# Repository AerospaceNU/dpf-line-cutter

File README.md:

# Line Cutter: For Cutting Lines
The line cutter is a system for deploying a single parachute as both drogue and main. Reefing lines are used to constrict the parachute to two intermediate sizes, and these lines are threaded through line cutters. At the set altitudes (or after a time delay), nichrome wires burn through the reefing lines.

## Organization
* `code`: Line cutter code and flight data analyses.
  * `launch archive`: Raw flight data and summaries of successes/failures from past line cutter flights. Subfolders should be named with ISO date and launch site.
  * `libraries and drivers`: Should be obsolete soon (drivers etc. will be published as Arduino libraries).
    * `openocd_windows.zip`: Windows build of openOCD with nrf52940 bootloader and cheap st-link config packaged.
  * `tests`: Code that is useful for testing various line cutter features across hardware versions.
  * `v1`: Code for v1 perfboard line cutters.
  * `v2`: Code for mixed perfboard and PCB line cutters.
  * `v3`: Code for current PCB line cutters.
    * `bulk_erase`: Erases all data on flash chip.
    * `flash_reader`: Reads all data on flash chip.
    * `flight_variable_upload`: Sets parameters for flight.
    * `identifier`: Names PCB for Bluetooth advertising.
    * `InternalFS_format`: Erases files on NRF52840 and formats filesystem.
    * `line_cutter_v3`: Main program that runs on flights.
    * `memory_reader`: Reads state transition log.
* `docs`: More detailed documentation, see below for list.
* `schematic`: ECAD files for the line cutter hardware. Contains schematics for all line cutter hardware. Folder structure is described in the [readme](schematic/README.md)

## Documentation
Code documentation applies to the latest version (v1/v2 are not compatible with current line cutters).
* [`CHECKLIST`](docs/CHECKLIST.md): Pre-flight checklist for line cutter launches.
* [`FLASH`](docs/FLASH.md): Procedure for logging data to flash on line cutters.
* [`SIGNALS`](docs/SIGNALS.md): Description of current board.
* [`STATES`](docs/STATES.md): Description of state machine.
* [`nrf52_openocd`](docs/nrf52_openocd.md): Instructions for programming NRF52 chips with OpenOCD.

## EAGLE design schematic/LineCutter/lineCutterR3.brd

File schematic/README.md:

# Line cutter schematics

This folder is organized as follows:
  * `batt-and-reg.cam`: CAM file used for JLC
  * `lineCutterR<N>-.zip`: Production files sent to fab
  * `LineCutter`: eagle project containing all the actual files
    * `Line Cutter COTS.lbr`: common parts used (flash memory, nRF daughterboards, etc)
    * `lineCutterR1`: first PCB ordered (nRF52832, December 2020)
    * `lineCutterR2`: ESP32-S2 based, ordered spring 2021 (1 built, no software written for it)
    * `lineCutterR3`: nRF52840-based, ordered spring 2021. Flew Amesbury 3/20.

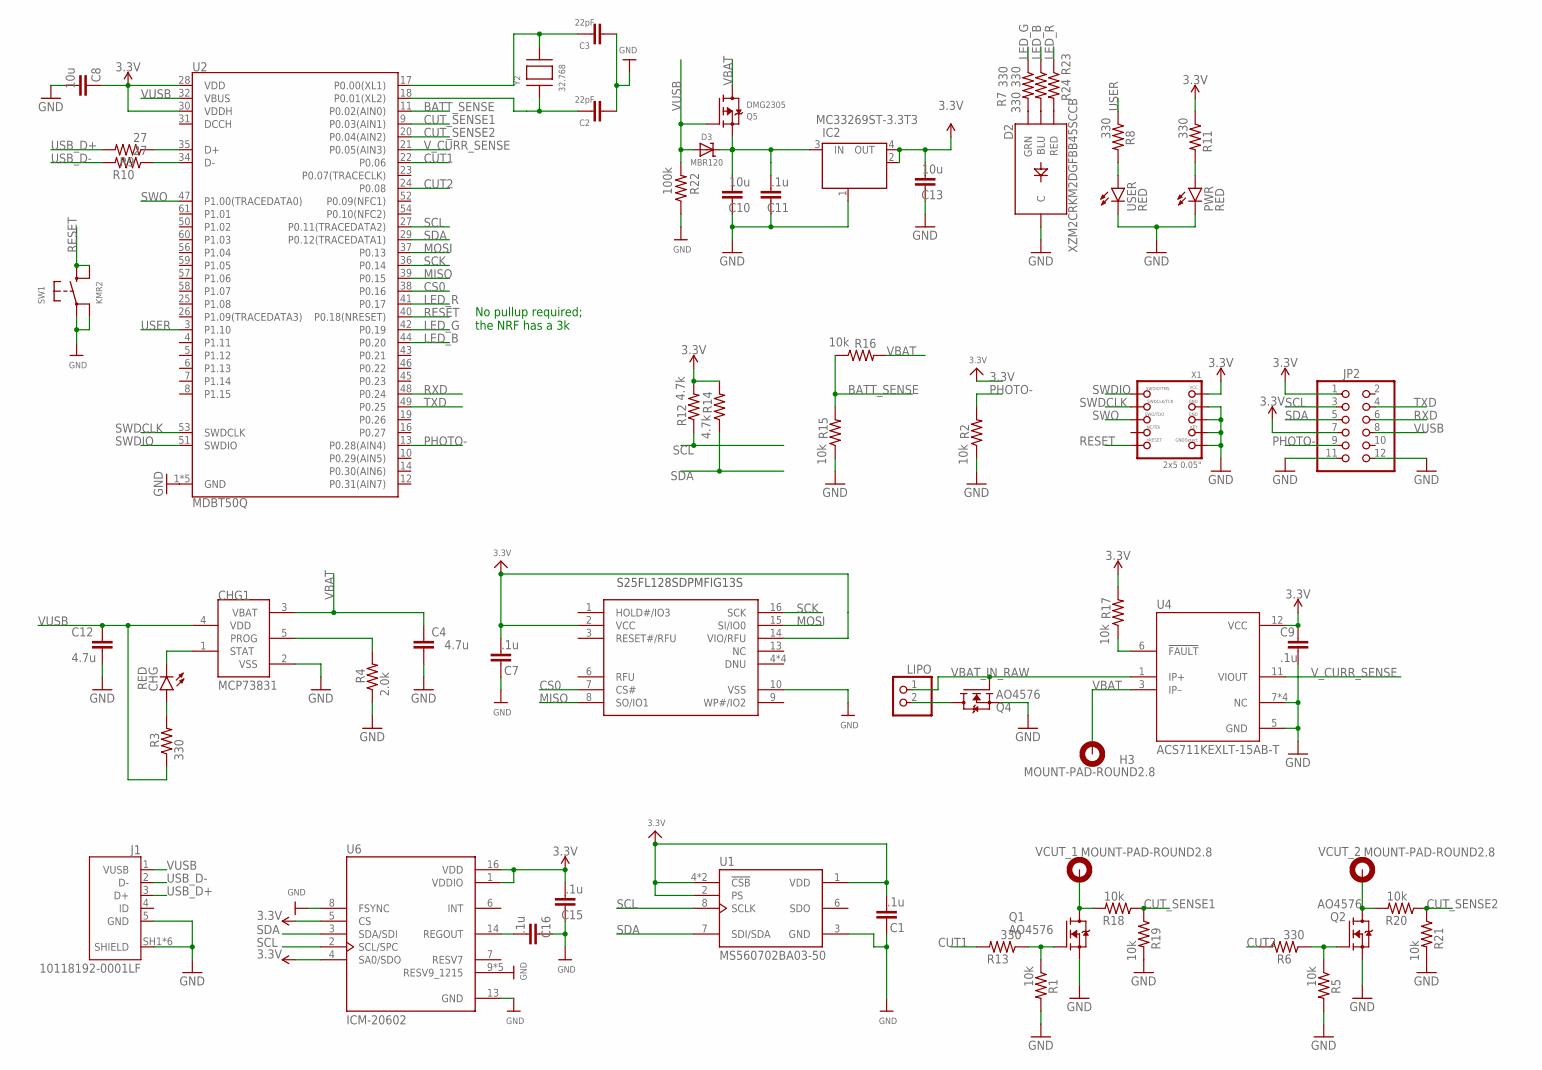
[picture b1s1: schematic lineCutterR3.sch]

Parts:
C1, C7, C9, C11, C15, C16: .1u; C0805
C2, C3: 22pF; C0805
C4, C12: 4.7u; C0805
C8, C10, C13: 10u; C0805
CHG: RED; CHIP-LED0805
CHG1: MCP73831; SOT23-5L
D2: XZM2CRKM2DGFBB45SCCB; PLCC4SMDLED
D3: MBR120; SOD-123
H3: MOUNT-PAD-ROUND2.8; 2,8-PAD
IC2: MC33269ST-3.3T3; SOT223
J1: 10118192-0001LF; AMPHENOL_10118192-0001LF
JP2: PINHD-2X6; 2X06
LIPO: PINHD-1X2; 1X02
PWR: RED; CHIP-LED0805
Q1, Q2, Q4: AO4576; SOIC8
Q5: DMG2305; SOT23-R
R1, R2, R5, R15, R16, R17, R18, R19, R20, R21: 10k; R0805
R3, R6, R7, R8, R11, R13, R23, R24: 330; R0805
R4: 2.0k; R0805
R9, R10: 27; R0805
R12, R14: 4.7k; R0805
R22: 100k; R0805
SW1: KMR2; BTN_KMR2_4.6X2.8
U1: MS560702BA03-50; SON125P300X500X100-8N
U2: MDBT50Q
U3: S25FL128SDPMFIG13S03016; SOIC127P1032X265-16N
U4: ACS711KEXLT-15AB-T; SENSOR_ACS711KEXLT-31AB-T
U6: ICM-20602; PQFN50P300X300X80-16N
USER: RED; CHIP-LED0805
VCUT_1, VCUT_2: MOUNT-PAD-ROUND2.8; 2,8-PAD
X1: 2x5 0.05"; 2X05_1.27MM_BOX_POSTS
Y2: 32.768; XTAL3215

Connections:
3.3V: C1.2, C7.2, C8.1, C9.1, C13.2, C15.2, IC2.2 (OUT), IC2.4 (OUT), JP2.1, JP2.7, R11.1, R12.2, R14.2, R17.2, U1.1 (VDD), U1.2 (PS), U1.4 (!CSB), U1.5 (!CSB), U2.28 (VDD), U2.30 (VDDH), U3.2 (VCC), U3.14 (VIO/RFU), U4.12 (VCC), U6.1 (VDDIO), U6.4 (SA0/SDO), U6.5 (CS), U6.16 (VDD), X1.1 (VCC)
BATT_SENSE: R15.2, R16.1, U2.11 (P0.02(AIN0))
CS0: U2.38 (P0.16), U3.7 (CS#)
CUT1: R13.2, U2.22 (P0.06)
CUT2: R6.2, U2.24 (P0.08)
CUT_SENSE1: R18.1, R19.1, U2.9 (P0.03(AIN1))
CUT_SENSE2: R20.1, R21.1, U2.20 (P0.04(AIN2))
GND: C1.1, C2.2, C3.2, C4.2, C7.1, C8.2, C9.2, C10.1, C11.1, C12.2, C13.1, C15.1, C16.1, CHG1.2 (VSS), D2.4 (C), IC2.1 (GND/ADJ), J1.5 (GND), J1.SH1 (SHIELD), J1.SH2 (SHIELD), J1.SH3 (SHIELD), J1.SH4 (SHIELD), J1.SH5 (SHIELD), J1.SH6 (SHIELD), JP2.11, JP2.12, PWR.C, Q1.P$1 (S), Q1.P$2 (S), Q1.P$3 (S), Q2.P$1 (S), Q2.P$2 (S), Q2.P$3 (S), Q4.P$1 (S), Q4.P$2 (S), Q4.P$3 (S), R1.2, R2.1, R4.1, R5.2, R15.1, R19.2, R21.2, R22.1, SW1.A, SW1.A' (P1), U1.3 (GND), U2.1 (GND), U2.2 (GND), U2.15 (GND), U2.33 (GND), U2.55 (GND), U3.10 (VSS), U4.5 (GND), U4.7 (NC), U4.8 (NC), U4.9 (NC), U4.10 (NC), U6.8 (FSYNC), U6.9 (RESV9_1215), U6.10 (RESV9_1215), U6.11 (RESV9_1215), U6.12 (RESV9_1215), U6.13 (GND), U6.15 (RESV9_1215), USER.C, X1.3 (GND), X1.5 (GND), X1.7 (KEY), X1.9 (GNDDETECT)
LED_B: R23.1, U2.44 (P0.20)
LED_G: R7.1, U2.42 (P0.19)
LED_R: R24.1, U2.41 (P0.17)
MISO: U2.39 (P0.15), U3.8 (SO/IO1)
MOSI: U2.37 (P0.13), U3.15 (SI/IO0)
unnamed: CHG.A, R3.2
unnamed: C2.1, U2.18 (P0.01(XL2)), Y2.P$1
unnamed: Q2.P$4 (G), R5.1, R6.1
unnamed: CHG1.5 (PROG), R4.2
unnamed: CHG.C, CHG1.1 (STAT)
unnamed: Q2.P$5 (D), Q2.P$6 (D), Q2.P$7 (D), Q2.P$8 (D), R20.2, VCUT_2.B2,8
unnamed: R8.2, USER.A
unnamed: LIPO.2, Q4.P$5 (D), Q4.P$6 (D), Q4.P$7 (D), Q4.P$8 (D)
unnamed: PWR.A, R11.2
unnamed: Q1.P$4 (G), R1.1, R13.1
unnamed: R9.1, U2.35 (D+)
unnamed: R10.1, U2.34 (D-)
unnamed: C3.1, U2.17 (P0.00(XL1)), Y2.P$2
unnamed: R17.1, U4.6 (!FAULT)
unnamed: D2.2 (GRN), R7.2
unnamed: D2.3 (BLU), R23.2
unnamed: Q1.P$5 (D), Q1.P$6 (D), Q1.P$7 (D), Q1.P$8 (D), R18.2, VCUT_1.B2,8
unnamed: D2.1 (RED), R24.2
unnamed: C16.2, U6.14 (REGOUT)
PHOTO-: JP2.9, R2.2, U2.13 (P0.28(AIN4))
RESET: SW1.B (S), SW1.B' (S1), U2.40 (P0.18(NRESET)), X1.10 (NRESET)
RXD: JP2.6, U2.48 (P0.24)
SCK: U2.36 (P0.14), U3.16 (SCK)
SCL: JP2.3, R12.1, U1.8 (SCLK), U2.27 (P0.11(TRACEDATA2)), U6.2 (SCL/SPC)
SDA: JP2.5, R14.1, U1.7 (SDI/SDA), U2.29 (P0.12(TRACEDATA1)), U6.3 (SDA/SDI)
SWDCLK: U2.53 (SWDCLK), X1.4 (SWDCLK)
SWDIO: U2.51 (SWDIO), X1.2 (SWDIO)
SWO: U2.47 (P1.00(TRACEDATA0)), X1.6 (SWO)
TXD: JP2.4, U2.49 (P0.25)
USB_D+: J1.3 (D+), R9.2
USB_D-: J1.2 (D-), R10.2
USER: R8.1, U2.3 (P1.10)
VBAT: C4.1, CHG1.3 (VBAT), H3.B2,8, Q5.3 (D), R16.2, U4.3 (IP–)
VBAT_IN_RAW: LIPO.1, Q4.P$4 (G), U4.1 (IP+)
VIN_REG1: C10.2, C11.2, D3.C, IC2.3 (IN), Q5.2 (S)
VUSB: C12.1, CHG1.4 (VDD), D3.A, J1.1 (VUSB), JP2.8, Q5.1 (G), R3.1, R22.2, U2.32 (VBUS)
V_CURR_SENSE: U2.21 (P0.05(AIN3)), U4.11 (VIOUT)

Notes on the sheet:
S25FL128SDPMFIG13S
No pullup required; the NRF has a 3k

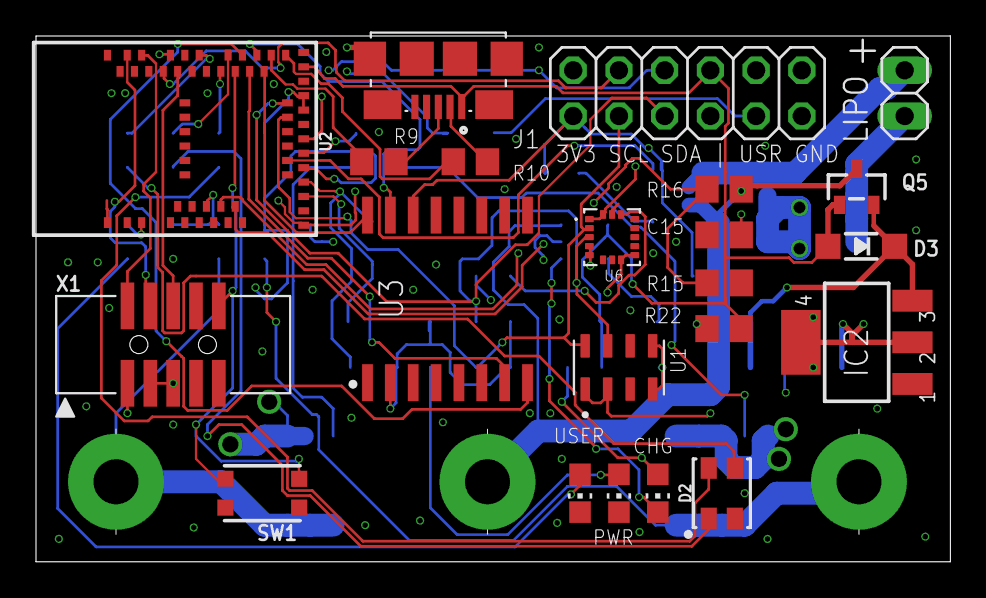
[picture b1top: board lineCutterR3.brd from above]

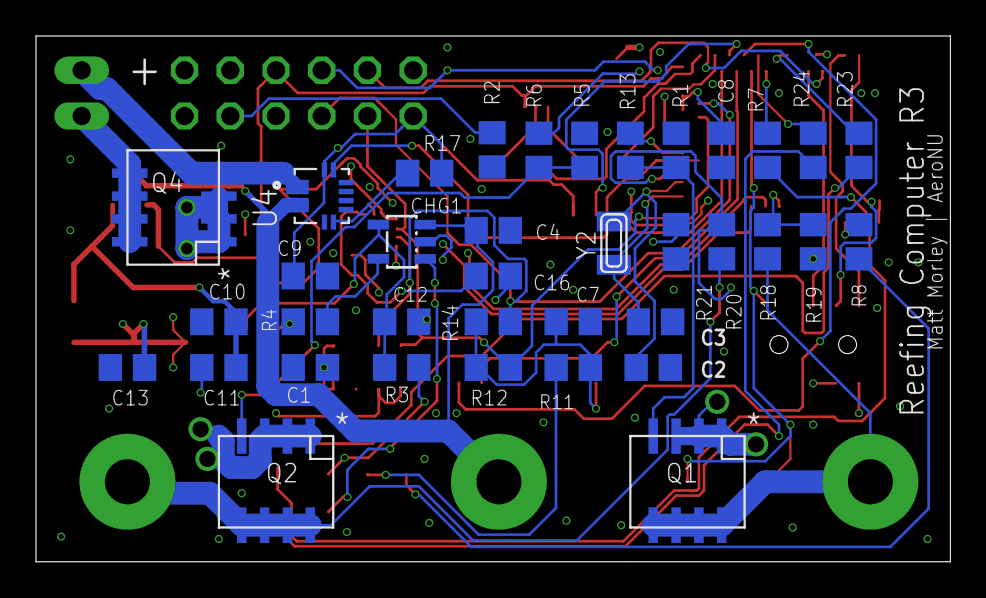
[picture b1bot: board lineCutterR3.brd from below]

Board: 4 copper layers, 50.8 x 29.2 mm, 62 parts (37 on the bottom side), 50 nets.

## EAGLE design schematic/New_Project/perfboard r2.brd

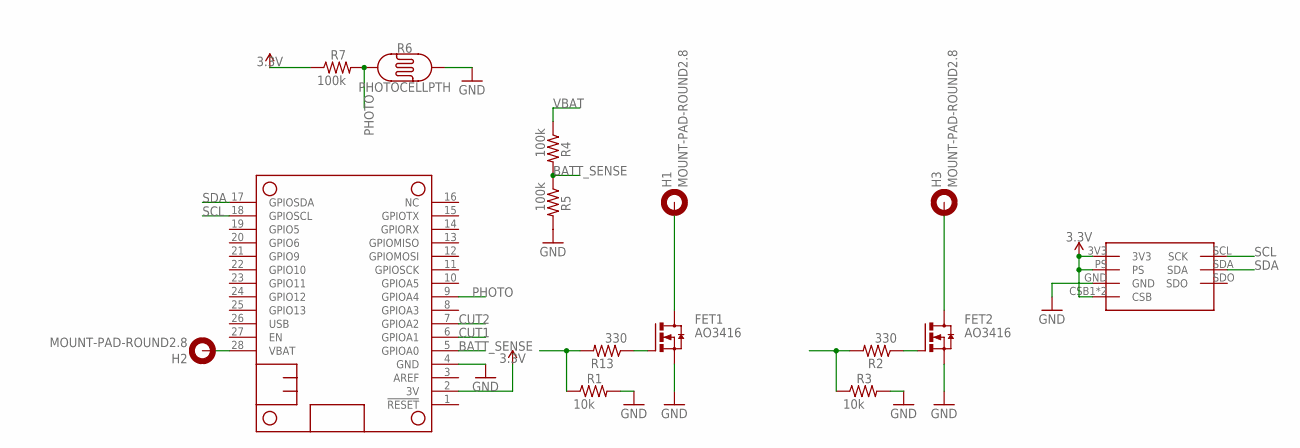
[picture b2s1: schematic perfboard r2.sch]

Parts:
FET1, FET2: AO3416; SOT23-3
H1, H2, H3: MOUNT-PAD-ROUND2.8; 2,8-PAD
MS1: FEATHERWING_NODIM
R1, R3: 10k; 0204/7
R2, R13: 330; 0204/7
R4, R5, R7: 100k; 0204/7
R6: PHOTOCELLPTH; PHOTOCELL
U$1: MS5607_BREAKOUT; MS5607BREAKOUT

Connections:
3.3V: MS1.2 (3V), R7.1, U$1.3V3, U$1.CSB1 (CSB), U$1.CSB2 (CSB), U$1.PS
BATT_SENSE: MS1.5 (GPIOA0), R4.2, R5.1
CUT1: MS1.6 (GPIOA1), R1.1, R13.2
CUT2: MS1.7 (GPIOA2), R2.2, R3.1
GND: FET1.2 (S), FET2.2 (S), MS1.4 (GND), R1.2, R3.2, R5.2, R6.2, U$1.GND
unnamed: FET1.3 (D), H1.B2,8
unnamed: FET2.1 (G), R2.1
unnamed: FET2.3 (D), H3.B2,8
unnamed: FET1.1 (G), R13.1
PHOTO: MS1.9 (GPIOA4), R6.1, R7.2
SCL: MS1.18 (GPIOSCL), U$1.SCL (SCK)
SDA: MS1.17 (GPIOSDA), U$1.SDA
VBAT: H2.B2,8, MS1.28 (VBAT), R4.1

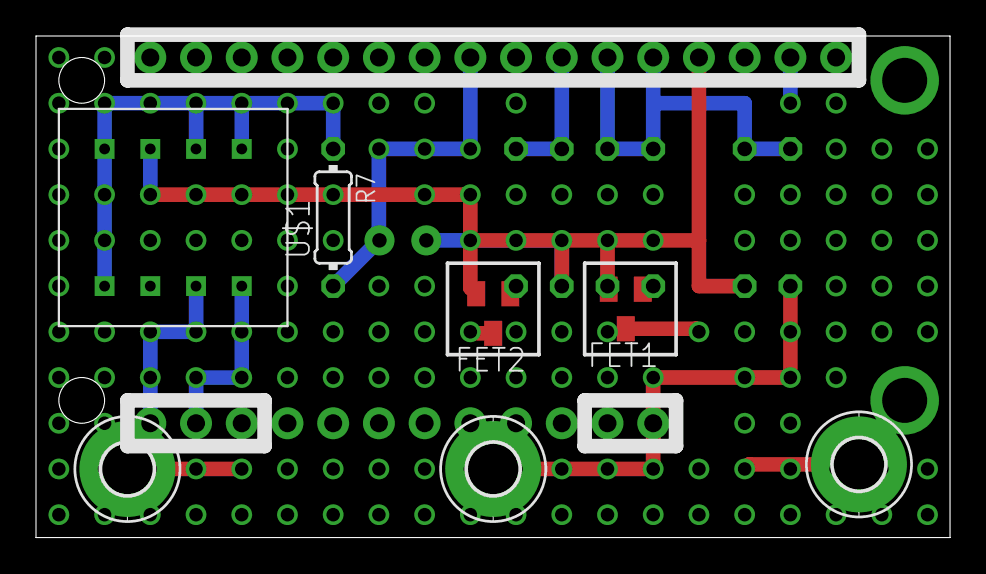
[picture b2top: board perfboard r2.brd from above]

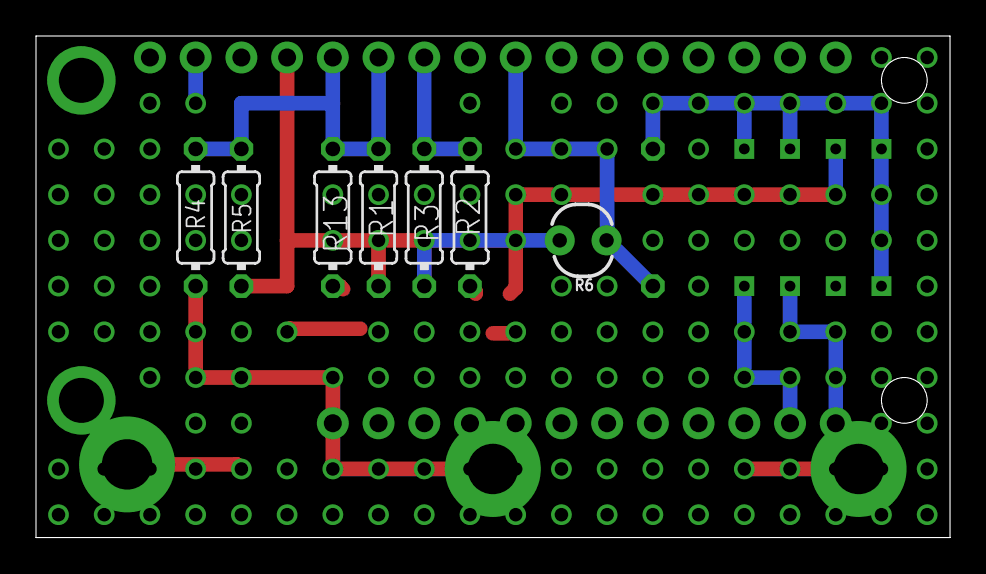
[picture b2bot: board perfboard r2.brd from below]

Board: 4 copper layers, 50.8 x 27.9 mm, 16 parts (7 on the bottom side), 13 nets.

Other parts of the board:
U$14: NRF52840_TOP

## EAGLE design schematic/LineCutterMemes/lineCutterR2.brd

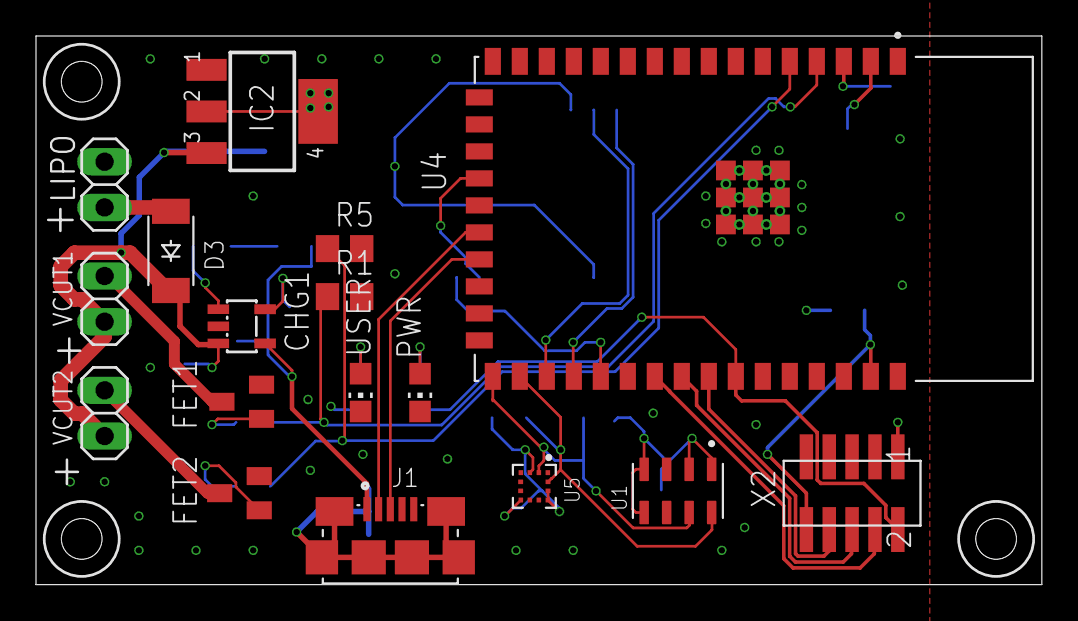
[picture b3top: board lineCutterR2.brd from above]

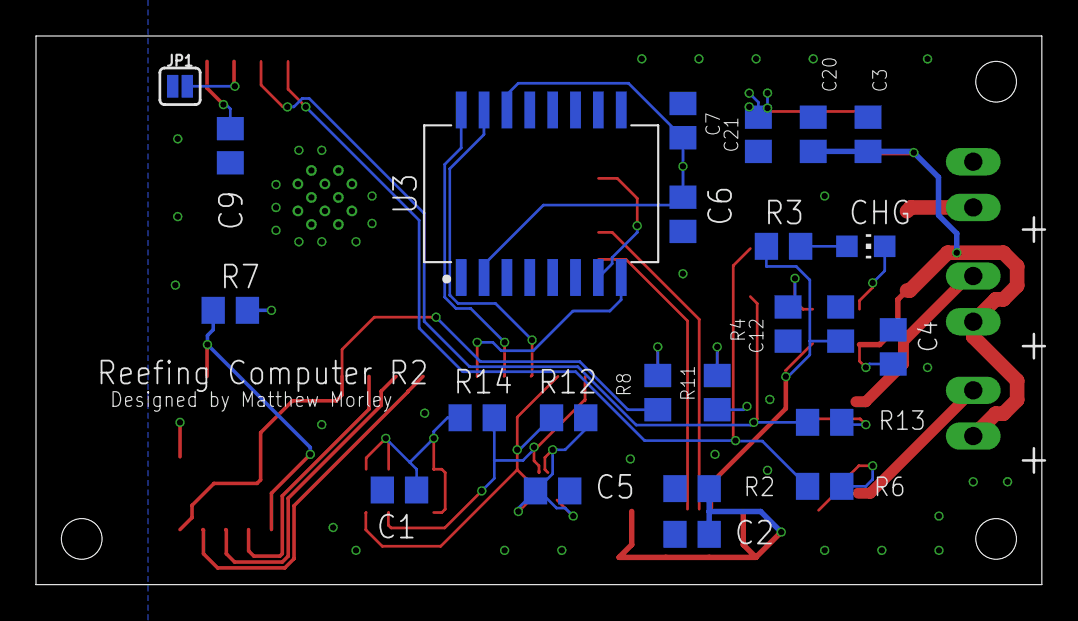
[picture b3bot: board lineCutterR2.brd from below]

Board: 4 copper layers, 55.9 x 30.5 mm, 41 parts (24 on the bottom side), 31 nets.

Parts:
C1, C5, C6, C7, C20, C21: .1u; C0805
C2: NF; C0805
C3: 10u; C0805
C4, C9, C12: 4.7u; C0805
CHG: RED; CHIP-LED0805
CHG1: MCP73831; SOT23-5L
D3: PMEG3050EP; SOD128
FET1, FET2: AO3416; SOT23-3
IC2: MC33269ST-3.3T3; SOT223
J1: 10118192-0001LF; AMPHENOL_10118192-0001LF
JP1: JUMPER-SMT_2_NO_SILK; SMT-JUMPER_2_NO_SILK
LIPO: 1X02
PWR: RED; CHIP-LED0805
R1, R5, R7: 10k; R0805
R2: NF; R0805
R3, R6, R8, R11, R13: 330; R0805
R4: 2.0k; R0805
R12, R14: 4.7k; R0805
U1: MS560702BA03-50; SON125P300X500X100-8N
U3: S25FL128SDPMFIG13S03016; SOIC127P1032X265-16N
U4: ESP32-S2-WROVER; MODULE_ESP32-S2-WROVER
U5: KXTJ3-1057; KIONIX_KXTJ3-1057
USER: RED; CHIP-LED0805
VCUT1, VCUT2: 1X02
X2: PIN-HEADER-MICRO-2-5-SMD; PIN-HEADER-NICRO-2-5-SMD

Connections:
3.3V: C1.2, C5.2, C6.2, C7.2, C9.1, C21.2, IC2.2, IC2.4, R7.2, R11.1, R12.2, R14.2, U1.1, U1.2, U1.4, U1.5, U3.2, U3.14, U4.2, U5.3, U5.7, U5.10, U5.11, X2.P$1
BL-RESET: R7.1, U4.41, X2.P$10
BOOT0: JP1.2, U4.3
CS0: U3.7, U4.20
CUT1: R1.1, R13.2, U4.4
CUT2: R5.1, R6.2, U4.5
GND: C1.1, C2.1, C3.1, C4.2, C5.1, C6.1, C7.1, C9.2, C12.2, C20.1, C21.1, CHG1.2, FET1.2, FET2.2, IC2.1, J1.5, JP1.1, LIPO.2, PWR.C, R1.2, R2.2, R4.1, R5.2, U1.3, U3.10, U4.1, U4.26, U4.42, U4.43_1, U4.43_2, U4.43_3, U4.43_4, U4.43_5, U4.43_6, U4.43_7, U4.43_8, U4.43_9, U4.43_10, U4.43_11, U4.43_12, U4.43_13, U4.43_14, U4.43_15, U4.43_16, U4.43_17, U4.43_18, U4.43_19, U4.43_20, U4.43_21, U5.1, U5.4, U5.6, U5.8, U5.9, USER.C, X2.P$3, X2.P$5, X2.P$7, X2.P$9
MISO: U3.8, U4.31
MOSI: U3.15, U4.29
unnamed: CHG.A, R3.2
unnamed: C2.2, J1.SH1, J1.SH2, J1.SH3, J1.SH4, J1.SH5, J1.SH6, R2.1
unnamed: FET2.1, R6.1
unnamed: CHG1.5, R4.2
unnamed: CHG.C, CHG1.1
unnamed: FET2.3, VCUT2.1
unnamed: PWR.A, R8.2
unnamed: D3.2, LIPO.1
unnamed: R11.2, USER.A
unnamed: FET1.1, R13.1
unnamed: FET1.3, VCUT1.1
SCK: U3.16, U4.30
SCL: R12.1, U1.8, U4.28, U5.12
SDA: R14.1, U1.7, U4.27, U5.2
TCK: U4.33, X2.P$4
TDI: U4.35, X2.P$8
TDO: U4.34, X2.P$6
TMS_D42: R8.1, U4.36, X2.P$2
USB_D+: J1.3, U4.23
USB_D-: J1.2, U4.22
VBAT: C3.2, C4.1, C20.2, CHG1.3, D3.1, IC2.3, VCUT1.2, VCUT2.2
VUSB: C12.1, CHG1.4, J1.1, R3.1

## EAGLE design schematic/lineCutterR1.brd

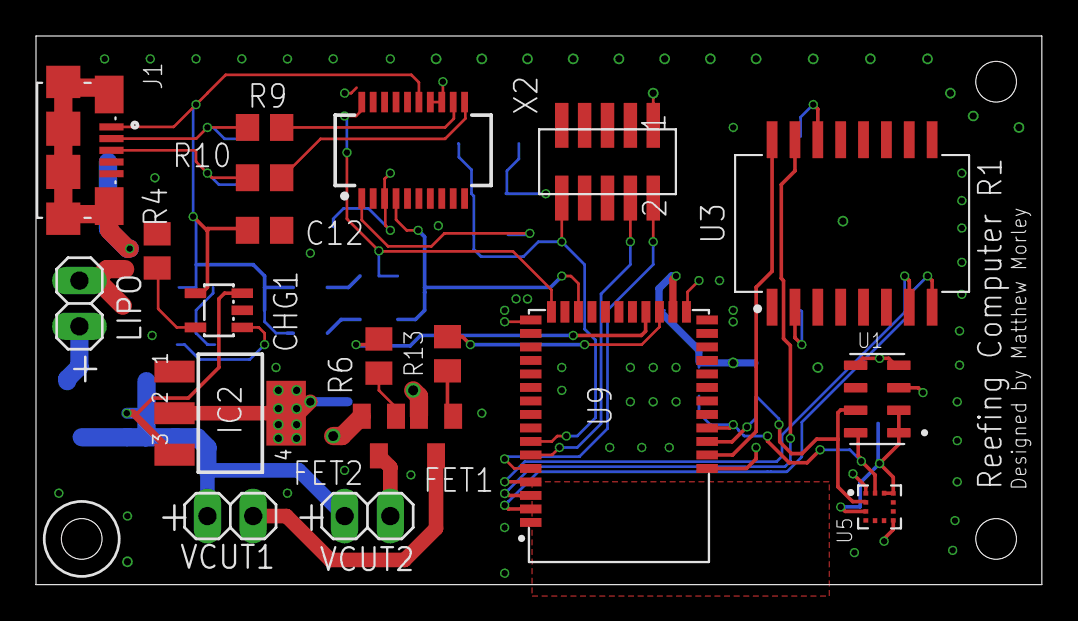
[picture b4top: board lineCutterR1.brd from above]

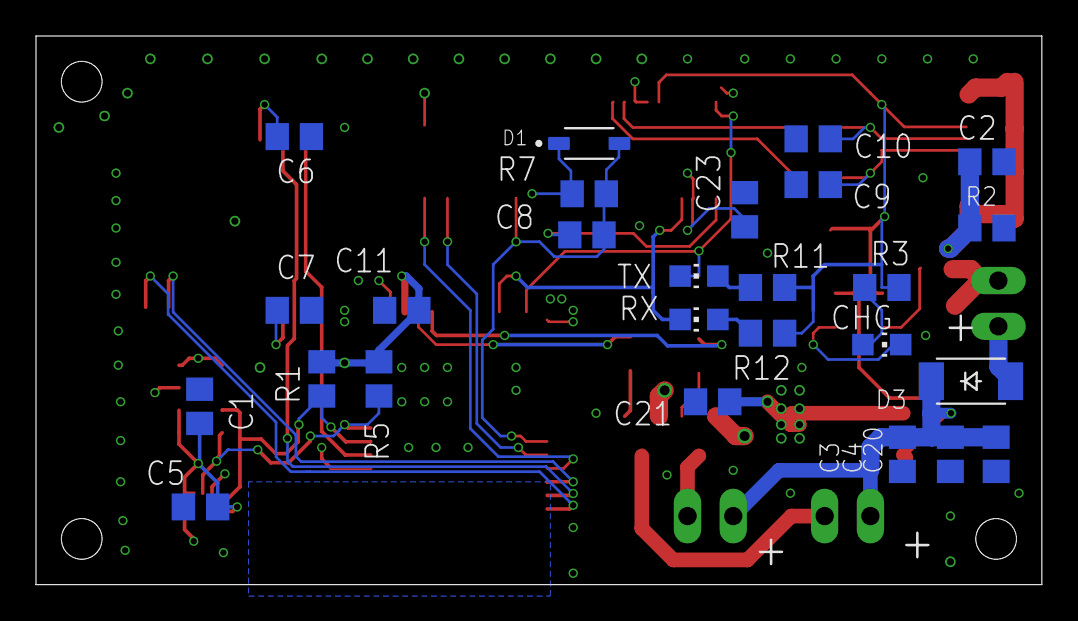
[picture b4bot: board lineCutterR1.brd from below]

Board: 4 copper layers, 55.9 x 30.5 mm, 46 parts (26 on the bottom side), 33 nets.

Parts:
C1, C5, C6, C7, C8, C11, C20, C21, C23: .1u; C0805
C2: NF; C0805
C3: 10u; C0805
C4, C12: 4.7u; C0805
C9, C10: 47p; C0805
CHG: RED; CHIP-LED0805
CHG1: MCP73831; SOT23-5L
D1: 1N4148W-7-F; SOD3715X135N
D3: PMEG3050EP; SOD128
FET1, FET2: AO3416; SOT23-3
IC2: MC33269ST-3.3T3; SOT223
J1: 10118192-0001LF; AMPHENOL_10118192-0001LF
LIPO: 1X02
R1, R5: 4.7k; R0805
R2: 1M; R0805
R3, R6, R13: 330; R0805
R4: 2.0k; R0805
R7: 10k; R0805
R9, R10: 27; R0805
R11, R12: 1k; R0805
RX: RED; CHIP-LED0805
TX: GREEN; CHIP-LED0805
U1: MS560702BA03-50; SON125P300X500X100-8N
U3: S25FL128SDPMFIG13S03016; SOIC127P1032X265-16N
U5: KXTJ3-1057; KIONIX_KXTJ3-1057
U8: FT231XS; SSOP20_L
U9: BL652-SA-01-T/R; XCVR_BL652-SA-01-T/R
VCUT1, VCUT2: 1X02
X2: PIN-HEADER-MICRO-2-5-SMD; PIN-HEADER-NICRO-2-5-SMD

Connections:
3.3V: C1.2, C5.2, C6.2, C7.2, C11.1, C21.2, C23.2, D1.C, IC2.2, IC2.4, R1.2, R5.2, R7.1, U1.1, U1.2, U1.4, U1.5, U3.2, U3.14, U5.3, U5.7, U5.10, U5.11, U8.3, U8.13, U8.14, U9.26, X2.P$1
BL-RESET: C8.1, D1.A, R7.2, U9.7, X2.P$10
BL-SWD-CLK: U9.6, X2.P$4
BL-SWD-IO: U9.5, X2.P$2
CS0: U3.7, U9.4
CUT1: R13.2, U9.25
CUT2: R6.2, U9.24
DTR: C8.2, U8.1
GND: C1.1, C2.1, C3.1, C4.2, C5.1, C6.1, C7.1, C9.2, C10.2, C11.2, C12.2, C20.1, C21.1, C23.1, CHG1.2, FET1.2, FET2.2, IC2.1, J1.5, LIPO.2, R2.2, R4.1, U1.3, U3.10, U5.1, U5.4, U5.6, U5.8, U5.9, U8.6, U8.16, U9.1, U9.16, U9.27, U9.28, U9.39, X2.P$3, X2.P$5, X2.P$9
MISO: U3.8, U9.2
MOSI: U3.15, U9.3
unnamed: CHG.A, R3.2
unnamed: C2.2, J1.SH1, J1.SH2, J1.SH3, J1.SH4, J1.SH5, J1.SH6, R2.1
unnamed: FET2.1, R6.1
unnamed: CHG1.5, R4.2
unnamed: CHG.C, CHG1.1
unnamed: FET2.3, VCUT2.1
unnamed: D3.2, LIPO.1
unnamed: FET1.1, R13.1
unnamed: R9.1, U8.12
unnamed: R10.1, U8.11
unnamed: FET1.3, VCUT1.1
unnamed: R11.2, TX.A
unnamed: R12.2, RX.A
RXD: TX.C, U8.20, U9.17
SCK: U3.16, U9.38
SCL: R5.1, U1.8, U5.12, U9.36
SDA: R1.1, U1.7, U5.2, U9.37
TXD: RX.C, U8.4, U9.19
USB_D+: C9.1, J1.3, R10.2
USB_D-: C10.1, J1.2, R9.2
VBAT: C3.2, C4.1, C20.2, CHG1.3, D3.1, IC2.3, VCUT1.2, VCUT2.2
VUSB: C12.1, CHG1.4, J1.1, R3.1, R11.1, R12.1, U8.15

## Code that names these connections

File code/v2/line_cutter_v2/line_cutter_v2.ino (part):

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char* stateStrings[5] = { "WAITING","DEPLOYED","PARTIAL_DISREEF","FULL_DISREEF","LANDED" };

// Pins. CHANGE FOR PERFBOARD VS PCB!
// PCB; A4 batt, 11 cut1, 12 cut2, A3 photo, PIN_LED2 for calibration
const int VOLTAGE_DIVIDER = A4;
const int NICHROME_PIN1 = 11;
const int NICHROME_PIN2 = 12;
const int PHOTO_PIN = A3;
const int CALIBRATION_LED = PIN_LED2;
// Perfboard; A0 batt, A1 cut1, A2 cut2, A4 photo, LED_BUILTIN for calibration
//const int VOLTAGE_DIVIDER = A0;
//const int NICHROME_PIN1 = A1;
//const int NICHROME_PIN2 = A2;
//const int PHOTO_PIN = A4;
//const int CALIBRATION_LED = LED_BUILTIN;

const int CUT_SENSE1 = A5;
const int CUT_SENSE2 = A0;
const int CURRENT_SENSE = A1;

// VARIABLES WHICH MUST BE SET
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  }

  // Photoresistor stuff
  light = analogRead(PHOTO_PIN);
  //Keep track of whether it is dark or light and for how long
  if(light > LIGHT_THRESHOLD)
    lastLightTime = loopStart;
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  currentData.pressure = baro.GetPres();
  currentData.temperature = baro.GetTemp();
  currentData.battSense = analogRead(VOLTAGE_DIVIDER);
  currentData.photoresistor = analogRead(PHOTO_PIN);
}

void updateFlash() {
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
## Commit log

2021-02-02 Add Feather code for perfboard line cutter
2021-02-03 commented my code lol
2021-02-03 enforced command structure
2021-02-04 I'm bad at git
2021-02-05 final version for car test
2021-02-09 started code for TRD (it's not functional)
2021-02-11 Add missing `;`
2021-02-14 explosion time
2021-02-14 I don't even know if I updated anything
2021-02-14 Add Melon MS5607 library
2021-02-14 Actually print pressure
2021-02-14 Add some comments
2021-02-15 implemented new PWM and barometer
2021-02-15 states and transitions
2021-02-16 fixed averaging library
2021-02-16 function descriptions
2021-02-16 elevator test version
2021-02-17 Create i2c test code for esp32s2
2021-02-17 Print time as well as line
    Not sure how helpful this will be -- bleuart seems to have a ton of lag
2021-02-17 Start on line cutter r3 hardware
2021-02-18 add ble, sealevel calibration w/ led
2021-02-18 oops
2021-02-18 loop delay mechanism + slower ble messages
2021-02-18 longer sea level sample
2021-02-23 Add esp32 test code for MS5607 and Melon driver
2021-02-24 Add esp 32 baro test with working MS5xxx
2021-02-25 Add bluetooth to esp32-baro-test
2021-02-25 Add Buck/Boost, RGB, Continuity, current sense
2021-02-28 final code for cert rocket tests
2021-02-28 R3 PCB: Place most of the components
2021-02-28 Add MS5xxx comments
2021-02-28 Fix variable typing in line-cutter-nrf
2021-02-28 add nrfAnalogWrite to line-cutter-nrf
2021-02-28 line-cutter-trd: adjust for cert rocket
2021-02-28 line-cutter-trd: implement nrfAnalogWrite
    Wheeeeeee
2021-02-28 Manually interact with HardwarePWM
    It's still being stupid, but in a way that doesn't seem to fail for us.
2021-03-01 Pass 1 at routing line cutter R3
2021-03-01 Final code from 2/28 LWHPR
2021-03-02 pwm resolution -> 8, renamed car test code folder
2021-03-03 Switch back to 3v3 lin reg
2021-03-03 line cutter v1 code to be preserved for all eternity
2021-03-04 Final board stuff
2021-03-08 Move stuff into a Project
2021-03-08 Create perfboard Eagle CAD
    Turns out CADing stuff helps
2021-03-08 Fix perfboard wiring
    No, A2 isnt supposed to drive PWM too -><-
2021-03-09 Reorg perfboard
2021-03-09 Add Internet Archive link to nrf52 doc
2021-03-09 Rename to LineCutterMemes
2021-03-14 Whee
2021-03-14 Add driver notes
2021-03-14 Fix photoresistor header
    Photo+ was not connected to 3v3
2021-03-15 Add code used to test flash, vddio
    Just some old code I had locally
2021-03-17 o r g a n i z a t i o n
2021-03-17 added libraries to v2 folder
2021-03-17 more organization
2021-03-17 even more organization (aka I
2021-03-17 Add ICM20602 driver
    Fullscale is kinda bjork
2021-03-17 folders
2021-03-18 Document board names
2021-03-18 ooooooooooooooops
2021-03-19 broken code
2021-03-19 Create self test
2021-03-19 not broken code
2021-03-19 identifier file
2021-03-19 no flash yet
2021-03-19 flash other than actual writing
2021-03-19 Add S25Fl driver ported from stm32-avionics
2021-03-20 added flash memory reader
2021-03-20 Send stuff slowly over bluetooth
2021-03-20 working(?) flash logging
2021-03-20 yay it probably works
2021-03-20 Add accelerometer
2021-03-20 final code uploaded for amesbury
2021-03-20 amesbury data
2021-03-23 updated amesbury flight logs with complete data
2021-03-29 flight data analysis
2021-03-30 updated flight summary
2021-03-30 split S25FL into .h and .cpp
2021-03-30 including libraries that it didn't need before??
2021-03-30 Add flash-based sketchy flight replay
2021-03-30 Fix flash compilation errors
2021-03-30 Use initializer list in flash construction
2021-03-31 simplification and separate PWM process
2021-03-31 flash writes from earliest empty sector
2021-04-02 added ble command routine
2021-04-04 removed wire begin from ms5xxx
2021-04-10 renamed car test file
2021-04-11 wrote bulk erase program
2021-04-11 flash location linear search
2021-04-11 explain code organization and docs
2021-04-11 added docs to docs folder
2021-04-11 info about hardware docs
2021-04-11 this code is broken
2021-04-12 flash documentation
2021-04-12 why is this code haunted
2021-04-12 ready to reset IDs
2021-04-12 prints time taken to bulk erase
2021-04-12 added state documentation
2021-04-12 Add README for schematic folder
2021-04-12 LineCutterMemes -> LineCutter
2021-04-14 Add openocd
2021-04-14 Further admonish users for forgetting to reset the nrf52
    Lookin at you, Matt
2021-04-16 add internal fs format code
2021-04-16 add openocd config files
2021-04-19 flash location and writing tested
2021-04-19 bulk erase tested
2021-04-19 read metadata and correct struct
2021-04-22 upload flight variables to InternalFS
2021-04-22 reads flight variables from InternalFS
2021-04-22 describe programs in v3 code folder
2021-04-24 prioritize reading ID
2021-04-24 final for amesbury 4/24
2021-04-24 fixed incorrect size for flash writes
2021-05-08 Add data from 5/7 drone test
2021-05-12 wrote pre-flight checklist
2021-05-15 added tcc day 1 data
2021-05-15 Reformat CSVs
    :/
2021-05-16 added TCC launch data
2021-05-16 fixed flash read formatting
2021-05-16 St. Alban's flight data added.
2021-05-16 St. Albans data
2021-05-16 St Albans flight analyis
2021-06-09 Add setup instructions
2021-06-09 added offload instructions
2021-06-22 Added June 20 TRD data
2021-06-28 Added installation pictures.
2021-06-28 Added instructions for installing line cutters on chute, including lots of pics
2021-06-30 trd flight summary graphs
2021-08-22 TRD Launch Data from St Albans on 08/21.
2021-08-22 Added launch summary for 08/21.
2021-10-10 marman clamp line cutter updates
2021-10-10 flight variable clarifications
2021-10-10 fixed issue where altitude is logged instead of delta
2021-10-10 user can input disreef altitudes for data logging
2021-10-10 added elevator test data
2021-10-10 added horizontal lines to elevator test chart
2021-10-10 Third elevator test
2021-10-11 new checklist for marman clamp launch
2021-10-13 pressure outlier filter
2021-10-23 Add simulator
2021-10-25 user can input disreef altitudes for plotting
2021-10-25 added data for 2021-10-24 launch
2021-10-25 added 2021-10-24 marman clamp code test data
2021-10-25 changed graphing window
2021-11-04 reinstated bluetooth arming
2021-11-05 Remove trailing zeros
2021-11-07 another approach to pressure filtering
2021-11-07 Add marmot flash replay
2021-11-09 Add simulated flight graph with updated arming logic
2021-11-10 updated checklist to include arming
2021-11-14 Revert "Add marmot flash replay"
    This reverts commit be64303dfef8dac543a06423e62b24b1166936dd.
2021-11-15 mdra data
2021-12-07 Create angry geese
2021-12-07 Rename
2021-12-09 Add elevator-tested code
2021-12-16 Reduce oversampling, switch back to apogee delay
2021-12-19 Add armed variable back
2021-12-21 Added Marman clamp release line cutter data from 12/19
2021-12-21 Added data from 12/19 for the line cutters on the chute
2022-04-14 Add !fcbdata and !fcbcfg
2022-04-14 Add support for Bluetooth firing in Armed
    Hook up to command
2022-04-15 Fix ble cutting code, maybe
2022-05-13 Refactor
2022-08-16 Fix build warnings in driver files
2022-09-12 Adding v4 code
2022-09-15 Most updated v3 code
2022-09-17 Change line cutter number and cut hardware pwm for cut 2
2022-09-17 Final preflight changes
2022-10-13 What Andy thinks we will be flying on 10-15 as long as Sam and people don't change it between now and then. Pin numbers adjusted to cause the correct channel to fire first. Flight variables updated.
2022-11-29 Master program for all little setup & memory reading tasks
2022-12-05 Add line_cutter_v3 and use more descriptive names
2022-12-21 Marman cutter redo
2022-12-21 Added documentation
2022-12-24 Added LC variant
2023-02-25 LC v4.1 updates
2023-02-27 LC updates
2023-03-19 Moved TVS diodes closer to connectors

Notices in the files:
parts and their libraries:
SparkFun-RF: Licensing: Creative Commons ShareAlike 4.0 International - https://creativecommons.org/licenses/by-sa/4.0
microbuilder: This work is placed in the public domain, and may be freely used for commercial and non-commercial work with the following conditions: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
